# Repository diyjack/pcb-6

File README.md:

# pcb
Eagle files for the TekVPI test fixture. Schematics, Board, and part libraries.
Requries Eagle 6.6.0 or above.

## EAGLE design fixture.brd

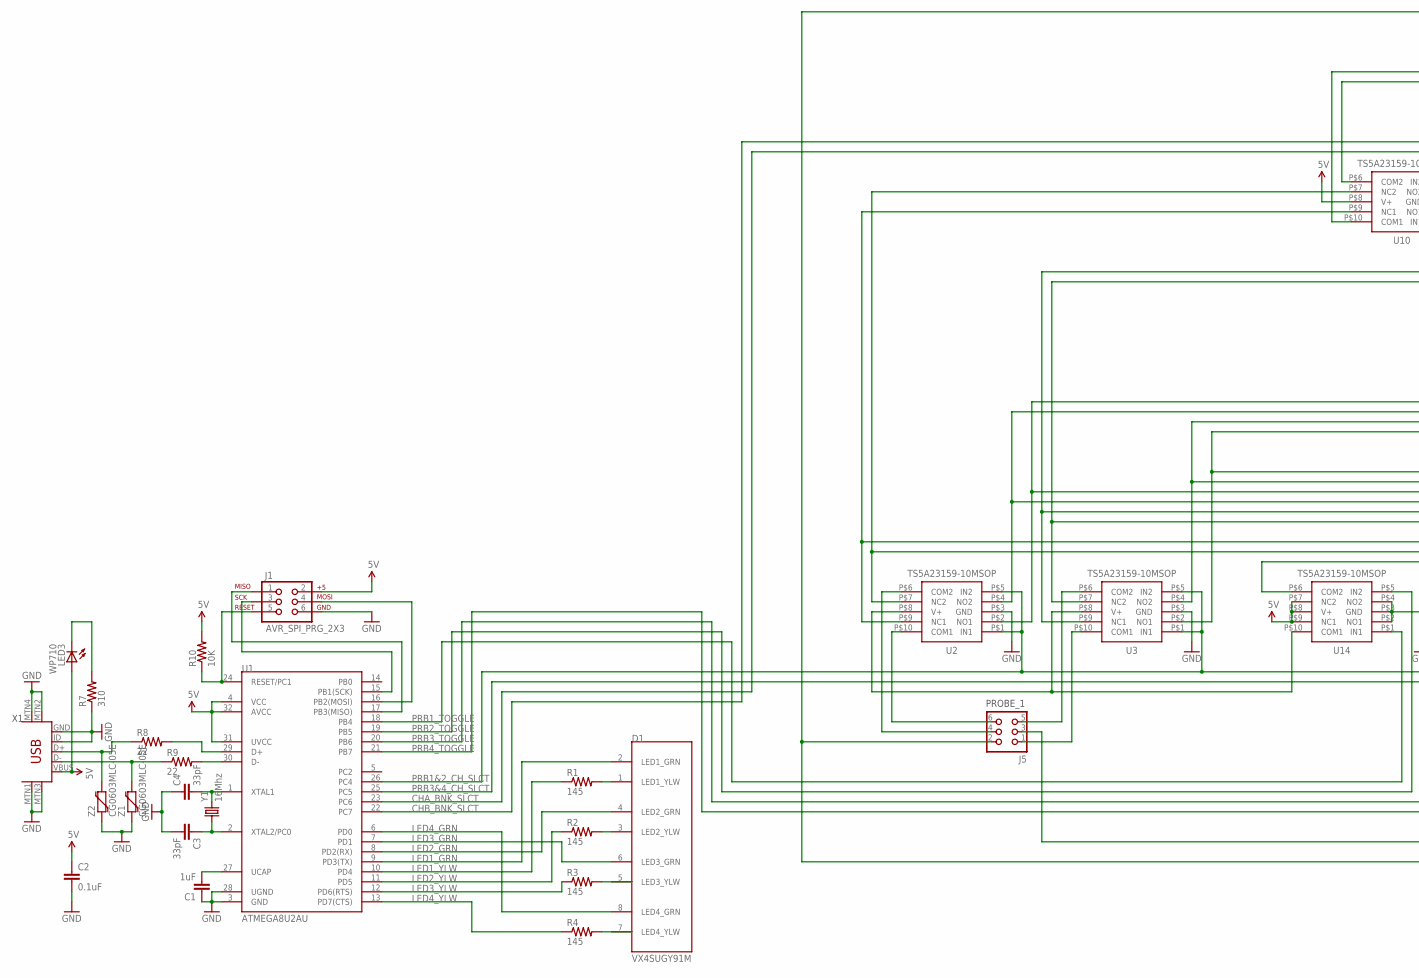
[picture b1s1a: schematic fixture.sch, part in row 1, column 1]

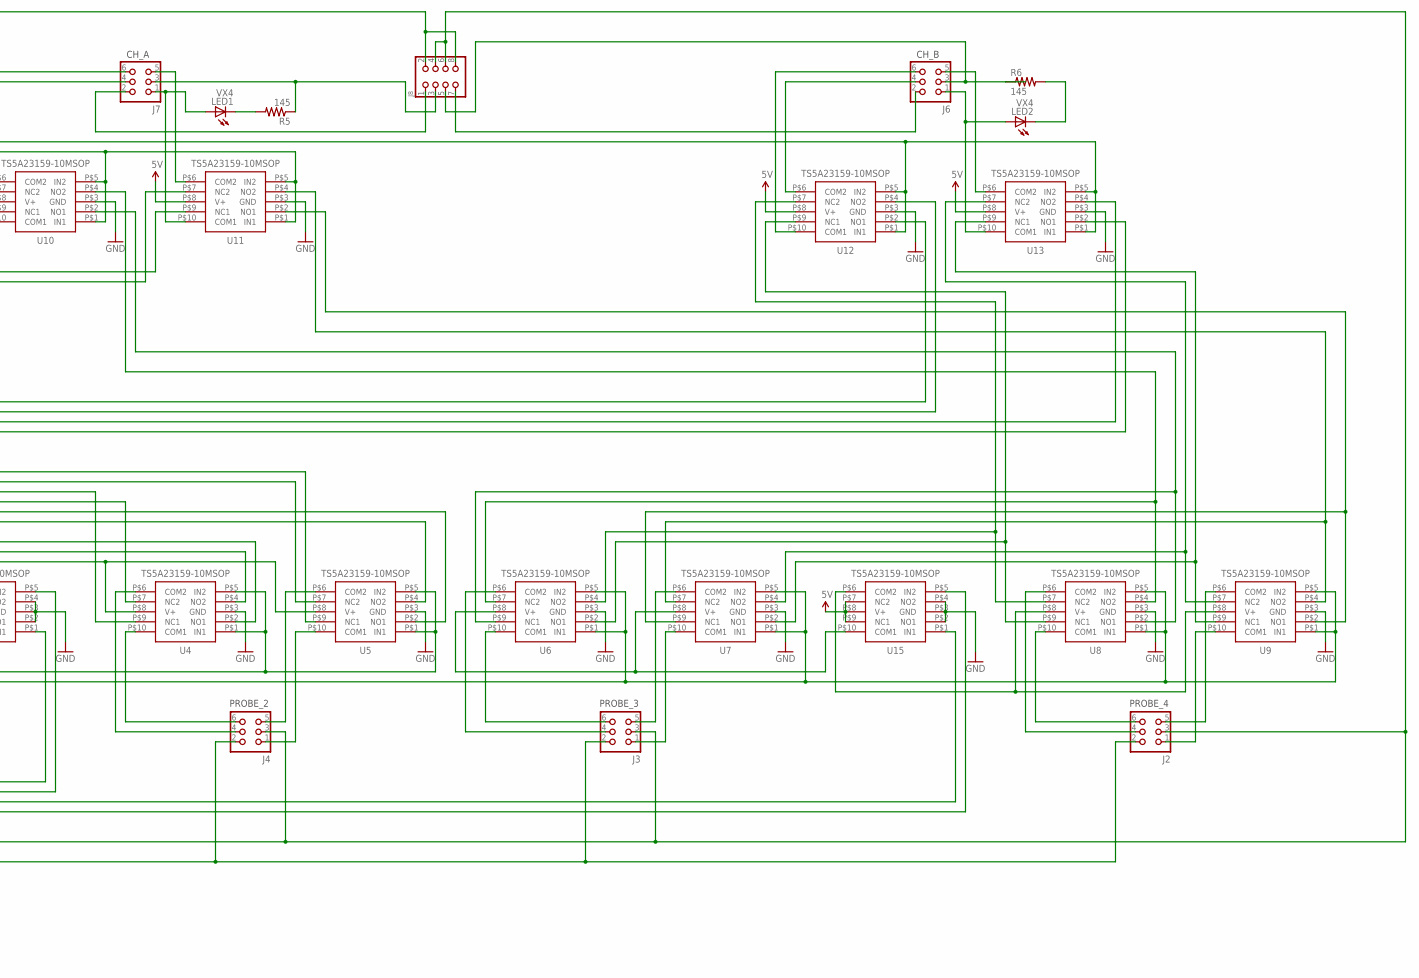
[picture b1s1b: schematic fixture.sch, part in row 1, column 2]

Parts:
C1: 1uF; 0603-CAP
C2: 0.1uF; 1206
C3, C4: 33pF; 0603-CAP
D1: VX4SUGY91M; THRU_HOLE
J1: AVR_SPI_PRG_2X3; 2X3
J2, J3, J4, J5, J6, J7: CON_HEADER_2X03-PTH; M2X3
J8: CON_HEADER_2X04-PTH; M2X4
LED1, LED2: VX4; LED3MM
LED3: WP710; LED3MM
R1, R2, R3, R4, R5, R6: 145; 0603-RES
R7: 310; 0603-RES
R8, R9: 22; 0603-RES
R10: 10K; 0603-RES
U1: ATMEGA8U2AU; TQFP32-08
U2, U3, U4, U5, U6, U7, U8, U9, U10, U11, U12, U13, U14, U15: TS5A23159-10MSOP; 10MSOP
X1: USB-MINIB-5PIN; USB-MINIB
Y1: 16Mhz; HC49US
Z1, Z2: CG0603MLC-05E; 0603-RES

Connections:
5V: C2.1, J1.2, LED3.A, R10.2, U1.4 (VCC), U1.31 (UVCC), U1.32 (AVCC), U10.P$8 (V+), U11.P$8 (V+), U12.P$8 (V+), U13.P$8 (V+), U14.P$7 (NC2), U14.P$8 (V+), U14.P$9 (NC1), U15.P$7 (NC2), U15.P$8 (V+), U15.P$9 (NC1), X1.VBUS
BOB123: U3.P$2 (NO1), U5.P$9 (NC1), U13.P$2 (NO1)
CHA_BNK_SLCT: U1.23 (PC6), U10.P$1 (IN1), U10.P$5 (IN2), U11.P$1 (IN1), U11.P$5 (IN2)
CHB_BNK_SLCT: U1.22 (PC7), U12.P$1 (IN1), U12.P$5 (IN2), U13.P$1 (IN1), U13.P$5 (IN2)
CH_A_+5CON: J7.1, LED1.A, U11.P$10 (COM1)
CH_A_BULK: J7.2, J8.1
CH_A_CLOCK: J7.6, U10.P$10 (COM1)
CH_A_DATA: J7.5, U11.P$6 (COM2)
CH_A_GND: J7.3, J8.3, R5.1
CH_A_INT: J7.4, U10.P$6 (COM2)
CH_B_+5CON: J6.1, LED2.A, U13.P$10 (COM1)
CH_B_BULK: J6.2, J8.7
CH_B_CLOCK: J6.6, U12.P$10 (COM1)
CH_B_DATA: J6.5, U13.P$6 (COM2)
CH_B_GND: J6.3, J8.5, R6.1
CH_B_INT: J6.4, U12.P$6 (COM2)
GND: C1.1, C2.2, C3.2, C4.1, J1.6, R7.1, U1.3 (GND), U1.28 (UGND), U2.P$3 (GND), U3.P$3 (GND), U4.P$3 (GND), U5.P$3 (GND), U6.P$3 (GND), U7.P$3 (GND), U8.P$3 (GND), U9.P$3 (GND), U10.P$3 (GND), U11.P$3 (GND), U12.P$3 (GND), U13.P$3 (GND), U14.P$2 (NO1), U14.P$3 (GND), U14.P$4 (NO2), U15.P$2 (NO1), U15.P$3 (GND), U15.P$4 (NO2), X1.GND, X1.ID, X1.MTN1 (MTN2), X1.MTN2 (MTN3), X1.MTN3 (MTN1), X1.MTN4, Z1.1, Z2.1
LED1_GRN: D1.2 (LED1_GRN), U1.9 (PD3(TX))
LED1_YLW: R1.1, U1.10 (PD4)
LED2_GRN: D1.4 (LED2_GRN), U1.8 (PD2(RX))
LED2_YLW: R2.1, U1.11 (PD5)
LED3_GRN: D1.6 (LED3_GRN), U1.7 (PD1)
LED3_YLW: R3.1, U1.12 (PD6(RTS))
LED4_GRN: D1.8 (LED4_GRN), U1.6 (PD0)
LED4_YLW: R4.1, U1.13 (PD7(CTS))
MISO: J1.1, U1.17 (PB3(MISO))
MOSI: J1.4, U1.16 (PB2(MOSI))
unnamed: R8.1, X1.D+, Z2.2
unnamed: R8.2, U1.29 (D+)
unnamed: R9.2, U1.30 (D-)
unnamed: R9.1, X1.D-, Z1.2
unnamed: C1.2, U1.27 (UCAP)
unnamed: U8.P$8 (V+), U9.P$8 (V+), U15.P$6 (COM2)
unnamed: C4.2, U1.1 (XTAL1), Y1.2
unnamed: C3.1, U1.2 (XTAL2/PC0), Y1.1
unnamed: U6.P$8 (V+), U7.P$8 (V+), U15.P$10 (COM1)
unnamed: D1.1 (LED1_YLW), R1.2
unnamed: D1.3 (LED2_YLW), R2.2
unnamed: D1.5 (LED3_YLW), R3.2
unnamed: D1.7 (LED4_YLW), R4.2
unnamed: U4.P$8 (V+), U5.P$8 (V+), U14.P$6 (COM2)
unnamed: LED1.K (C), R5.2
unnamed: LED2.K (C), R6.2
unnamed: U7.P$2 (NO1), U9.P$9 (NC1), U13.P$9 (NC1)
unnamed: U7.P$4 (NO2), U9.P$7 (NC2), U13.P$7 (NC2)
unnamed: U6.P$2 (NO1), U8.P$9 (NC1), U12.P$9 (NC1)
unnamed: U6.P$4 (NO2), U8.P$7 (NC2), U12.P$7 (NC2)
unnamed: U7.P$9 (NC1), U9.P$2 (NO1), U11.P$2 (NO1)
unnamed: U7.P$7 (NC2), U9.P$4 (NO2), U11.P$4 (NO2)
unnamed: U6.P$9 (NC1), U8.P$2 (NO1), U10.P$2 (NO1)
unnamed: U6.P$7 (NC2), U8.P$4 (NO2), U10.P$4 (NO2)
unnamed: U3.P$9 (NC1), U5.P$2 (NO1), U11.P$9 (NC1)
unnamed: U3.P$7 (NC2), U5.P$4 (NO2), U11.P$7 (NC2)
unnamed: U2.P$9 (NC1), U4.P$2 (NO1), U10.P$9 (NC1)
unnamed: U2.P$7 (NC2), U4.P$4 (NO2), U10.P$7 (NC2)
unnamed: U2.P$4 (NO2), U4.P$7 (NC2), U12.P$4 (NO2)
unnamed: U2.P$2 (NO1), U4.P$9 (NC1), U12.P$2 (NO1)
unnamed: U3.P$4 (NO2), U5.P$7 (NC2), U13.P$4 (NO2)
unnamed: LED3.K (C), R7.2
PRB1&2_CH_SLCT: U1.26 (PC4), U2.P$1 (IN1), U2.P$5 (IN2), U3.P$1 (IN1), U3.P$5 (IN2), U4.P$1 (IN1), U4.P$5 (IN2), U5.P$1 (IN1), U5.P$5 (IN2)
PRB1_TOGGLE: U1.18 (PB4), U14.P$1 (IN1)
PRB2_TOGGLE: U1.19 (PB5), U14.P$5 (IN2)
PRB3&4_CH_SLCT: U1.25 (PC5), U6.P$1 (IN1), U6.P$5 (IN2), U7.P$1 (IN1), U7.P$5 (IN2), U8.P$1 (IN1), U8.P$5 (IN2), U9.P$1 (IN1), U9.P$5 (IN2)
PRB3_TOGGLE: U1.20 (PB6), U15.P$1 (IN1)
PRB4_TOGGLE: U1.21 (PB7), U15.P$5 (IN2)
PROBE1_+5CON: J5.1, U3.P$10 (COM1)
PROBE1_CLOCK: J5.6, U2.P$10 (COM1)
PROBE1_DATA: J5.5, U3.P$6 (COM2)
PROBE1_INT: J5.4, U2.P$6 (COM2)
PROBE1_PWR: U2.P$8 (V+), U3.P$8 (V+), U14.P$10 (COM1)
PROBE2_+5CON: J4.1, U5.P$10 (COM1)
PROBE2_CLOCK: J4.6, U4.P$10 (COM1)
PROBE2_DATA: J4.5, U5.P$6 (COM2)
PROBE2_INT: J4.4, U4.P$6 (COM2)
PROBE3_+5CON: J3.1, U7.P$10 (COM1)
PROBE3_CLOCK: J3.6, U6.P$10 (COM1)
PROBE3_DATA: J3.5, U7.P$6 (COM2)
PROBE3_INT: J3.4, U6.P$6 (COM2)
PROBE4_+5CON: J2.1, U9.P$10 (COM1)
PROBE4_CLOCK: J2.6, U8.P$10 (COM1)
PROBE4_DATA: J2.5, U9.P$6 (COM2)
PROBE4_INT: J2.4, U8.P$6 (COM2)
RESET: J1.5, R10.1, U1.24 (RESET/PC1)
SCK: J1.3, U1.15 (PB1(SCK))
SCOPE_BULK: J2.2, J3.2, J4.2, J5.2, J8.2, J8.8
SCOPE_GND: J2.3, J3.3, J4.3, J5.3, J8.4, J8.6

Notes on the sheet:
CH_A
CH_B
PROBE_1
PROBE_2
PROBE_3
PROBE_4

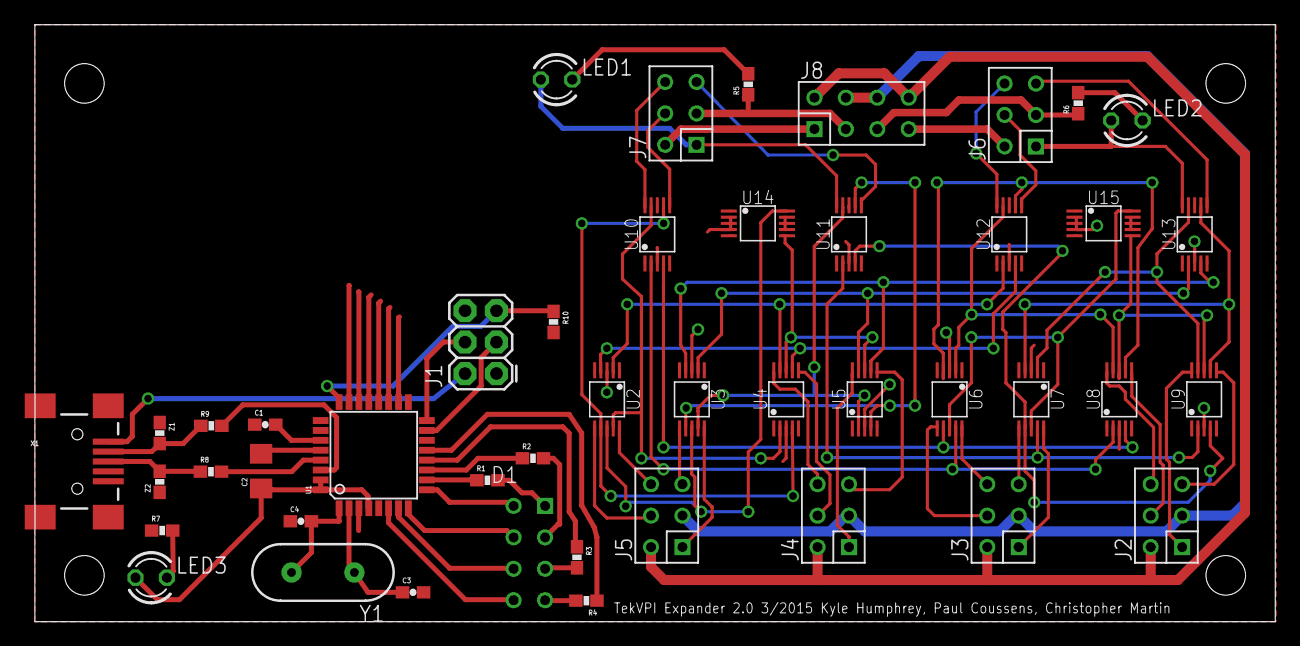
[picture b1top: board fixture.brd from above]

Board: 2 copper layers, 100.3 x 48.2 mm, 45 parts (0 on the bottom side), 86 nets.

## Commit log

2015-02-22 version 8.2 of the PCB. Changes to LED I/O, LED library file and added silkscreen info.

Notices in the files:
parts and their libraries:
SparkFun-DigitalIC: Licensing: Creative Commons ShareAlike 4.0 International - https://creativecommons.org/licenses/by-sa/4.0
